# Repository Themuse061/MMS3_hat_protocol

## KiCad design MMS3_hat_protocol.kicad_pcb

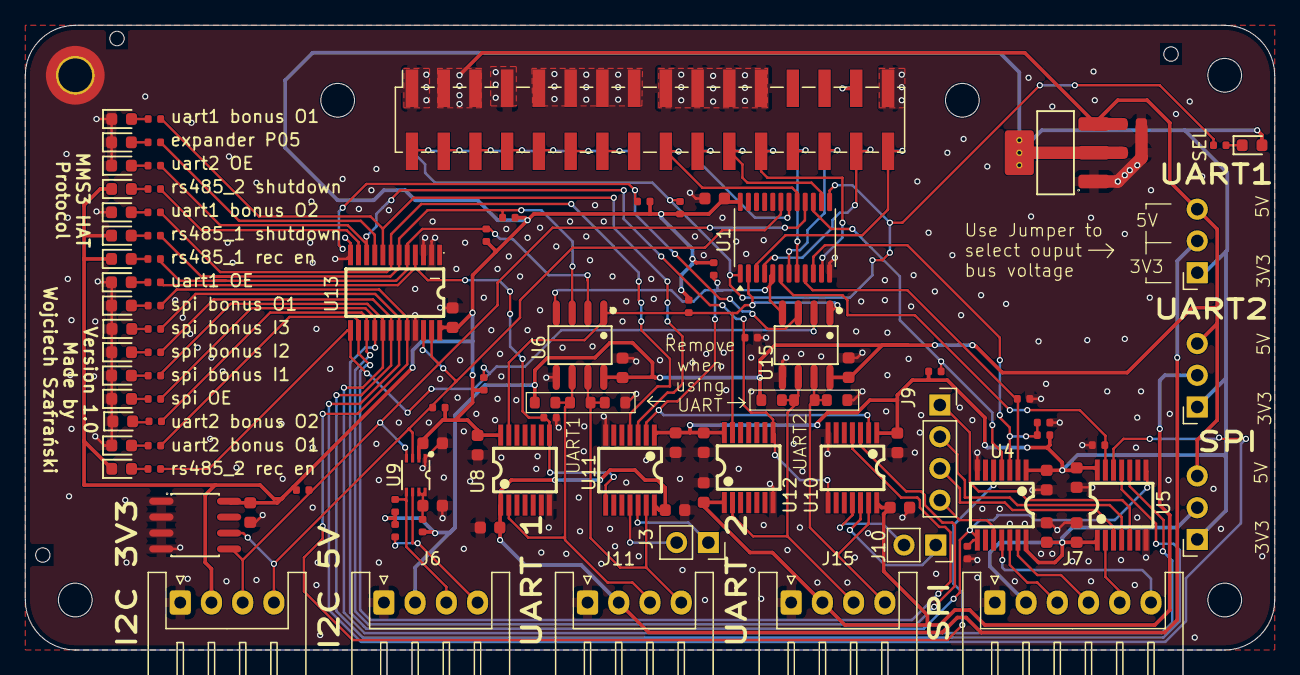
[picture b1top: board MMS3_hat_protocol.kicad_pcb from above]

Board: 2 copper layers, 100.0 x 50.0 mm, 116 parts (1 on the bottom side), 84 nets.

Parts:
C1, C2, C4, C6, C7, C8, C9, C10, C11, C12, C13, C14, C15, C17, C18, C19, C20, C21, C22: 100nF; C_0603
C3, C5: 10uF; C_0603
D6, D7, D8, D9, D10, D15, D16, D17, D18, D19, D20, D21, D22, D23, D24, D25, D26: Red; D_0603
H1: M2.5 Mount; MountingHole_2.7mm_M2.5_DIN965_Pad_TopOnly
H2, H3, H4, H5, H6: M2.5 mount; MountingHole_2.7mm_M2.5
H7, H8, H9: Hole_Tooling_JLCPCB
J1: Chainbus in; PinHeader_2x16_P2.54mm_Vertical_SMD
J2: Chainbus Out; PinSocket_2x16_P2.54mm_Vertical_SMD
J3, J10: Conn_01x02_Pin; PinSocket_1x02_P2.54mm_Vertical
J4, J6, J11, J15: Conn_01x04_Pin; JST_XH_S4B-XH-A_1x04_P2.50mm_Horizontal
J5, J8, J14: Conn_01x03_Pin; PinSocket_1x03_P2.54mm_Horizontal
J7: Conn_01x06_Pin; JST_XH_S6B-XH-A_1x06_P2.50mm_Horizontal
J9: Conn_01x04_Pin; PinSocket_1x04_P2.54mm_Vertical
R2, R3, R4, R6, R8, R9, R10, R11, R15, R16, R17, R18, R19, R20, R22, R38, R40, R42, R44: 10kΩ; R_0402
R5, R12, R13, R14, R21, R37, R39, R41, R43, R45, R46, R47, R48, R49, R50, R51, R52: 330Ω; R_0402
R7: 200kΩ; R_0402
R23, R24, R26, R27: 510Ω; R_0603
R25, R28: 120Ω; R_0603
U1: SN74CB3Q3384APW; TSSOP-24_4.4x7.8mm_P0.65mm
U2: M24C64; SOIC-8_L5.0-W4.0-P1.27-LS6.0-BL
U3: AMS1117; SOT-223-3_L6.5-W3.4-P2.30-LS7.0-BR
U4, U5, U8, U10, U11, U12: TXU0104PWR; TSSOP-14_L5.0-W4.4-P0.65-LS6.4-BL
U6, U15: MAX13487EESA; SOIC-8_L4.9-W3.9-P1.27-LS6.0-BL
U9: PCA9306DCUR; SSOP-8_L2.0-W2.3-P0.50-LS3.1-BR
U13: TCA9535PWR_C130204; TSSOP-24_L7.8-W4.4-P0.65-LS6.4-BL

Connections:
+3V3: C1.1, C2.1, C4.1, C5.1, C6.1, C8.1, C9.1, C11.1, C15.1, C18.1, C20.1, D6.2, D15.1, D16.1, D17.1, D18.1, J4.2, J5.1, J8.1, J14.1, R2.1, R3.1, R15.1, R16.1, R17.1, R19.1, R22.2, R38.2, R40.2, R42.2, R44.2, U1.24 (VCC), U2.8 (VCC), U3.2 (VOUT), U3.4 (VOUT), U4.1 (VCCA), U5.14 (VCCB), U8.14 (VCCB), U9.2 (VREF1), U10.1 (VCCA), U11.1 (VCCA), U12.14 (VCCB), U13.24 (VCC)
+5V: C3.1, C12.1, C14.1, J1.3, J1.5, J2.3, J2.5, J5.3, J6.2, J8.3, J14.3, R7.2, R8.1, R9.1, R23.2, R24.2, U3.3 (VIN), U6.8 (VCC), U15.8 (VCC)
+12V stby: J1.29, J2.29
/Bus_switch/Chainbus_In.CS: J1.22, J2.22, U1.14 (2A1)
/Bus_switch/Chainbus_In.MISO: J1.28, J2.28, U1.7 (1A3)
/Bus_switch/Chainbus_In.MOSI: J1.26, J2.26, U1.8 (1A4)
/Bus_switch/Chainbus_In.RX: J1.32, J2.32, U1.3 (1A1)
/Bus_switch/Chainbus_In.SCK: J1.24, J2.24, U1.11 (1A5)
/Bus_switch/Chainbus_In.SCL: J1.20, J2.20, U1.18 (2A3)
/Bus_switch/Chainbus_In.SDA: J1.18, J2.18, U1.17 (2A2)
/Bus_switch/Chainbus_In.TX: J1.30, J2.30, U1.4 (1A2)
/Bus_switch/SEL1: J1.2, R21.1, R22.1, U1.1 (~1OE), U1.13 (~2OE)
/Chainbus.CS: R2.2, U1.15 (2B1), U4.4 (A3)
/Chainbus.MISO: R18.1, U1.6 (1B3), U5.13 (B1Y)
/Chainbus.MOSI: R20.1, U1.9 (1B4), U4.2 (A1)
/Chainbus.RX: R17.2, U1.2 (1B1), U6.1 (RO), U8.13 (B1Y), U12.13 (B1Y), U15.1 (RO)
/Chainbus.SCK: R3.2, R4.1, U1.10 (1B5), U4.3 (A2)
/Chainbus.SCL: J4.4, R15.2, U1.19 (2B3), U2.6 (SCL), U9.3 (SCL1), U13.22 (SCL)
/Chainbus.SDA: J4.3, R19.2, U1.16 (2B2), U2.5 (SDA), U9.4 (SDA1), U13.23 (SDA)
/Chainbus.TX: R16.2, U1.5 (1B2), U6.4 (DI), U10.2 (A1), U11.2 (A1), U15.4 (DI)
/Interboard_connector/SEL2: J1.4, J2.2
/Interboard_connector/SEL3: J1.6, J2.4
/Interboard_connector/SEL4: J1.8, J2.6
/Interboard_connector/SEL5: J1.10, J2.8
/Interboard_connector/SEL6: J1.12, J2.10
/Interboard_connector/SEL7: J1.14, J2.12
/Interboard_connector/SEL8: J1.16, J2.14
/P00: R11.1, R12.1, U8.8 (OE), U11.8 (OE), U13.4 (P00)
/P01: R39.1, R40.1, U6.2 (~RE), U13.5 (P01)
/P02: R37.1, R38.1, U6.3 (~SHDN), U13.6 (P02)
/P03: R45.1, U11.4 (A3), U13.7 (P03)
/P04: R46.1, U11.3 (A2), U13.8 (P04)
/P05: R5.1, U13.9 (P05)
/P06: R10.1, R13.1, U10.8 (OE), U12.8 (OE), U13.10 (P06)
/P07: R43.1, R44.1, U13.11 (P07), U15.3 (~SHDN)
/P10: R41.1, R42.1, U13.13 (P10), U15.2 (~RE)
/P11: R47.1, U10.4 (A3), U13.14 (P11)
/P12: R48.1, U10.3 (A2), U13.15 (P12)
/P13: R6.1, R14.1, U4.8 (OE), U5.8 (OE), U13.16 (P13)
/P14: R51.1, U5.10 (B4Y), U13.17 (P14)
/P15: R52.1, U5.11 (B3Y), U13.18 (P15)
/P16: R49.1, U5.12 (B2Y), U13.19 (P16)
/P17: R50.1, U4.5 (A4), U13.20 (P17)
/SPI 1/Bonus_IN_1_SEL: J9.3, U5.3 (A2)
/SPI 1/Bonus_IN_2_SEL: J9.2, U5.4 (A3)
/SPI 1/Bonus_IN_3_SEL: J9.1, U5.5 (A4)
/SPI 1/Bonus_OUT_1_SEL: J9.4, U4.10 (B4Y)
/SPI 1/CS_SEL: J7.6, U4.11 (B3Y)
/SPI 1/MISO_SEL: J7.5, U5.2 (A1)
/SPI 1/MOSI_SEL: J7.4, U4.13 (B1Y)
/SPI 1/SCK_SEL: J7.3, U4.12 (B2Y)
/SPI 1/V_SEL: C7.1, C10.1, J5.2, J7.2, U4.14 (VCCB), U5.1 (VCCA)
/UART 1/Bonus_OUT_1_SEL: J3.1, U11.12 (B2Y)
/UART 1/Bonus_OUT_2_SEL: J3.2, U11.11 (B3Y)
/UART 1/RS485_A: J11.3, R23.1, R25.2, U6.6 (A), U8.2 (A1)
/UART 1/RS485_B: J11.4, R25.1, R26.2, U6.7 (B), U11.13 (B1Y)
/UART 1/V_SEL: C13.1, C17.1, J8.2, J11.2, U8.1 (VCCA), U11.14 (VCCB)
/UART 2/Bonus_OUT_1_SEL: J10.1, U10.12 (B2Y)
/UART 2/Bonus_OUT_2_SEL: J10.2, U10.11 (B3Y)
/UART 2/RS485_A: J15.3, R24.1, R28.2, U12.2 (A1), U15.6 (A)
/UART 2/RS485_B: J15.4, R27.2, R28.1, U10.13 (B1Y), U15.7 (B)
/UART 2/V_SEL: C19.1, C21.1, J14.2, J15.2, U10.14 (VCCB), U12.1 (VCCA)
/Vref2: C22.1, R7.1, U9.7 (VREF2), U9.8 (EN)
BRD_VIN: J1.9, J1.11, J1.13, J1.15, J2.9, J2.11, J2.13, J2.15
GND: C1.2, C2.2, C3.2, C4.2, C5.2, C6.2, C7.2, C8.2, C9.2, C10.2, C11.2, C12.2, C13.2, C14.2, C15.2, C17.2, C18.2, C19.2, C20.2, C21.2, C22.2, D7.1, D8.1, D9.1, D10.1, D19.1, D20.1, D21.1, D22.1, D23.1, D24.1, D25.1, D26.1, H1.1 (1_1), J1.1, J1.7, J1.17, J1.19, J1.21, J1.23, J1.31, J2.1, J2.7, J2.17, J2.19, J2.21, J2.23, J2.31, J4.1, J6.1, J7.1, J11.1, J15.1, R4.2, R6.2, R10.2, R11.2, R18.2, R20.2, R26.1, R27.1, U1.12 (GND), U2.1 (A0), U2.2 (A1), U2.3 (A2), U2.4 (VSS), U3.1 (GND), U4.7 (GND), U5.7 (GND), U6.5 (GND), U8.7 (GND), U9.1 (GND), U10.7 (GND), U11.7 (GND), U12.7 (GND), U13.2 (A1), U13.3 (A2), U13.12 (GND), U13.21 (A0), U15.5 (GND)
unnamed: D6.1, R21.2
unnamed: D7.2, R5.2
unnamed: D8.2, R12.2
unnamed: D9.2, R13.2
unnamed: D10.2, R14.2
unnamed: D15.2, R37.2
unnamed: D16.2, R39.2
unnamed: D17.2, R41.2
unnamed: D18.2, R43.2
unnamed: D19.2, R45.2
unnamed: D20.2, R46.2
unnamed: D21.2, R47.2
unnamed: D22.2, R48.2
unnamed: D23.2, R49.2
unnamed: D24.2, R50.2
unnamed: D25.2, R51.2
unnamed: D26.2, R52.2
unnamed: J6.3, R9.2, U9.5 (SDA2)
unnamed: J6.4, R8.2, U9.6 (SCL2)

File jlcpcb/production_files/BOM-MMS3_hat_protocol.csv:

Comment,Designator,Footprint,LCSC,Quantity
100nF,"C1,C10,C11,C12,C13,C14,C15,C17,C18,C19,C2,C20,C21,C22,C4,C6,C7,C8,C9",C_0603,C14663,19
10kΩ,"R10,R11,R15,R16,R17,R18,R19,R2,R20,R22,R3,R38,R40,R42,R44,R6,R8,R9",R_0402,C25744,18
10uF,"C3,C5",C_0603,C19702,2
120Ω,"R25,R28",R_0603,C22787,2
200kΩ,R7,R_0402,C25764,1
330Ω,"R12,R13,R14,R21,R37,R39,R41,R43,R45,R46,R47,R48,R49,R5,R50,R51,R52",R_0402,C25104,17
510Ω,"R23,R24,R26,R27",R_0603,C23193,4
AMS1117,U3,SOT-223-3_L6.5-W3.4-P2.30-LS7.0-BR,C6186,1
M24C64,U2,SOIC-8_L5.0-W4.0-P1.27-LS6.0-BL,C79988,1
MAX13487EESA,"U15,U6",SOIC-8_L4.9-W3.9-P1.27-LS6.0-BL,C18347,2
PCA9306DCUR,U9,SSOP-8_L2.0-W2.3-P0.50-LS3.1-BR,C33196,1
Red,"D10,D15,D16,D17,D18,D19,D20,D21,D22,D23,D24,D25,D26,D6,D7,D8,D9",D_0603,C2286,17
SN74CB3Q3384APW,U1,TSSOP-24_4.4x7.8mm_P0.65mm,C469874,1
TCA9535PWR_C130204,U13,TSSOP-24_L7.8-W4.4-P0.65-LS6.4-BL,C130204,1
TXU0104PWR,"U10,U11,U12,U4,U5,U8",TSSOP-14_L5.0-W4.4-P0.65-LS6.4-BL,C2938871,6
Conn_01x02_Pin,J10,PinSocket_1x02_P2.54mm_Vertical,,1
Conn_01x04_Pin,J9,PinSocket_1x04_P2.54mm_Vertical,,1
Chainbus Out,J2,PinSocket_2x16_P2.54mm_Vertical_SMD,,1
Conn_01x03_Pin,J5,PinSocket_1x03_P2.54mm_Horizontal,,1
Conn_01x02_Pin,J3,PinSocket_1x02_P2.54mm_Vertical,,1
~,H8,Hole_Tooling_JLCPCB,,1
Conn_01x04_Pin,J15,JST_XH_S4B-XH-A_1x04_P2.50mm_Horizontal,,1
~,H7,Hole_Tooling_JLCPCB,,1
Conn_01x03_Pin,J14,PinSocket_1x03_P2.54mm_Horizontal,,1
Conn_01x04_Pin,J11,JST_XH_S4B-XH-A_1x04_P2.50mm_Horizontal,,1
Conn_01x04_Pin,J4,JST_XH_S4B-XH-A_1x04_P2.50mm_Horizontal,,1
Conn_01x06_Pin,J7,JST_XH_S6B-XH-A_1x06_P2.50mm_Horizontal,,1
~,H9,Hole_Tooling_JLCPCB,,1
Conn_01x04_Pin,J6,JST_XH_S4B-XH-A_1x04_P2.50mm_Horizontal,,1
Chainbus in,J1,PinHeader_2x16_P2.54mm_Vertical_SMD,,1

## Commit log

2026-03-07 schematic done
2026-04-18 most routing done
2026-04-18 finished routing
2026-04-21 test commit
